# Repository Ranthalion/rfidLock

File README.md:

View this project on [CADLAB.io](https://cadlab.io/project/1244). 

# rfidLock
RFID Lock system

###Lock Hardware
The lock is [Morning Industry RF-01SN](https://www.amazon.com/gp/product/B000FBU2KW "Morning Industry RF-01SN").

###Lamp Server
Primary Network IP: 10.200.200.11 up on eth0   
Secure Network IP: 172.12.123.20 up on eth1   
Software: Apache2, php7 w/all mods and oauth extension, mariaDB, phpMyAdmin   
Services: SSHD   

### Diagram

### Database Diagram

### Installation

#### Configuration File

A configuration file is necessary for managing the connection to the mysql 
database which is used as the authoratative data source. This file is also 
needed for other configuration details such as the location of templates.

The options that can be configured in this file's database parameter match with mysql.connector's 
[Python Connection Arguments](https://dev.mysql.com/doc/connector-python/en/connector-python-connectargs.html)

A simple example configuration file is shown here for reference.

```json
{
  "database": {
    "username": "rfid_user",
    "password": "db_passwd",
    "host": "rfid_host",
    "database": "rfid_db"
  },
  "templates": "/usr/share/rfidlock/templates"
}
```

#### Member Server

To install the member server and web interface:

```bash
git clone https://github.com/Ranthalion/rfidLock.git
sudo pip install rfidLock/
# Edit or create the config.json file described above
vim /etc/rfidlock/config.json
# Creates the necessary database tables
rfid_db_install

# For Arch, this should enable wsgi
echo "LoadModule wsgi_module modules/mod_wsgi.so" >> /etc/httpd/conf/httpd.conf
# For Debian/Ubuntu, this should enable wsgi
a2enmod wsgi

# Mount the WSGI script, again, this is for Arch, will be different on other distros
echo "WSGIScriptAlias /rfid_db.wsgi $(which rfid_db.wsgi)" >> /etc/httpd/conf/httpd.conf

# Install and enable mod_wsgi
# Modify Apache server configuration

# TODO run a script that installs an apache server site to a path
# Varies by distribution

# ? WSGIScriptAlias /wsgi /path/to/script/rfid_members.wsgi
# TODO configure apache server to run mod_wsgi
```

To remove the member server after installation:

#### Raspberry Pi
Secure Network IP: 172.12.123.98
```bash
git clone https://github.com/Ranthalion/rfidLock.git
sudo pip install rfidLock/
# TODO, establish a daemon that handles the RFID lock and enable it on start-up
```

## Web API

### GET /api/verify  
Verifies access to a resource by rfid  
#### Consumes 
This API call consumes the following media types via the Content-Type request header:  
application/x-www-form-urlencoded  
#### Query parameters  
**resource (required)**  
Query Parameter — The name of the resource being requested  
**encryptedrfid (optional)**  
Query Parameter — The encoded rfid value  
**rfid (optional)**  
Query Parameter — The raw, unencoded rfid value  
#### Return type  
Content-Type: application/json  
```
{
  "verified" : false
}
```

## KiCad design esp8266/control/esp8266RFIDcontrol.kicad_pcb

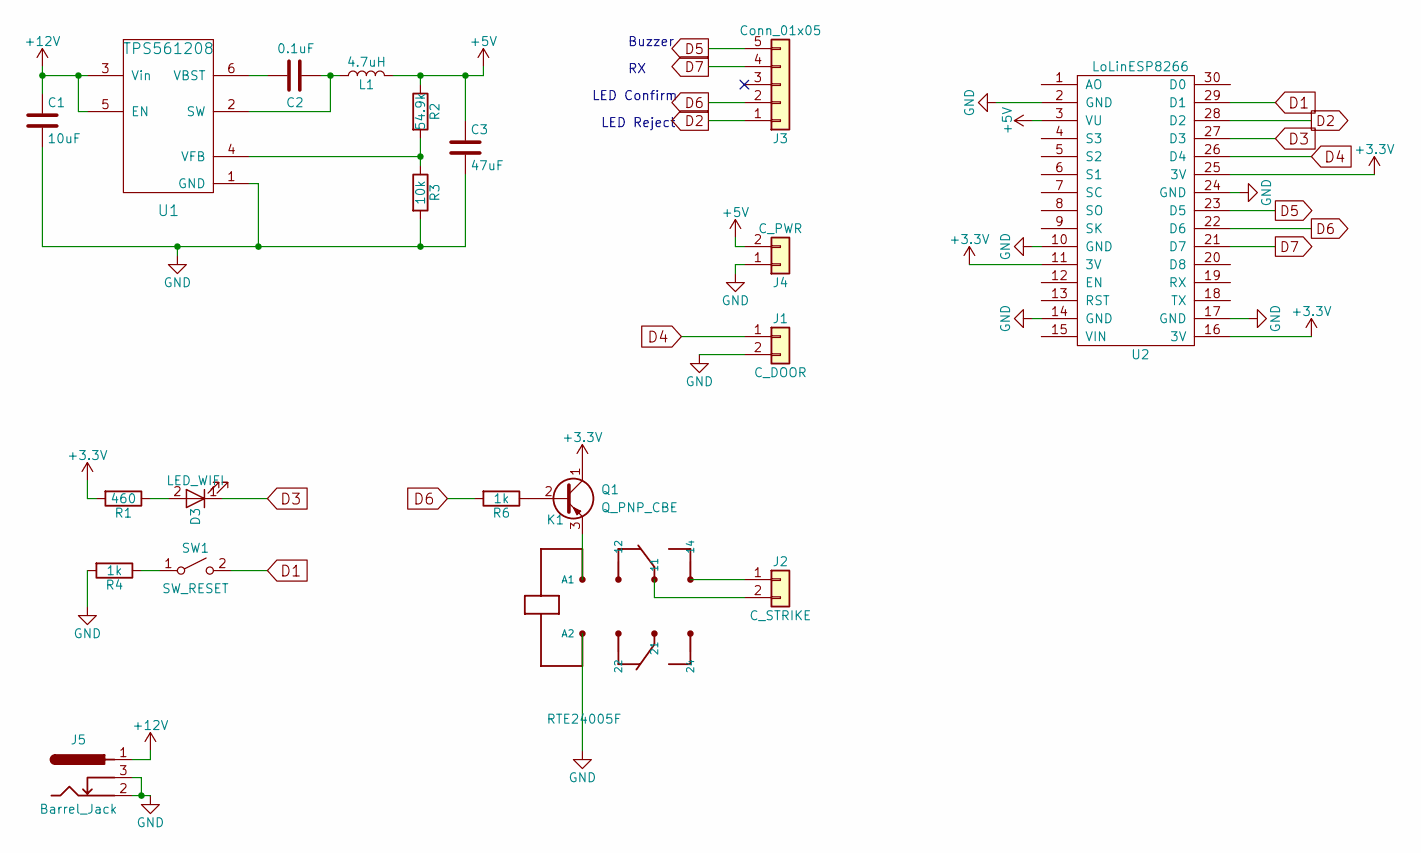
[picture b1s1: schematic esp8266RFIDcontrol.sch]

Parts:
C1: 10uF; C_1210_HandSoldering
C2: 0.1uF; C_1206_HandSoldering
C3: 47uF; C_1210_HandSoldering
D3: LED_WIFI; LED_0603_HandSoldering
J1: C_DOOR; CONNECTOR_JST_SH_2
J2: C_STRIKE; TerminalBlock_bornier-2_P5.08mm
J3: Conn_01x05; CONNECTOR_JST_SH_5
J4: C_PWR; CONNECTOR_JST_SH_2
J5: Barrel_Jack; BARREL_JACK
K1: RTE24005F
L1: 4.7uH; L_Wuerth_HCI-5040
Q1: Q_PNP_CBE; SOT-23_Handsoldering
R1: 460; R_0805_HandSoldering
R2: 54.9k; R_0805_HandSoldering; Tolerance 1%
R3: 10k; R_0805_HandSoldering; Tolerance 1%
R4, R6: 1k; R_0805_HandSoldering
SW1: SW_RESET; button_smd_2_pin
U1: TPS561208; SOT-23-6_Handsoldering
U2: LoLinESP8266; LOLIN_NODEMCU

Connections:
+3V3: Q1.1 (C), R1.2, U2.11 (3V), U2.16 (3V), U2.25 (3V)
+5V: C3.1, J4.2, L1.2, R2.1, U2.3 (VU)
+12V: C1.1, J5.1, U1.3 (Vin), U1.5 (EN)
D1: SW1.2 (B), U2.29 (D1)
D2: J3.1, U2.28 (D2)
D3: D3.1 (K), U2.27 (D3)
D4: J1.1, U2.26 (D4)
D5: J3.5, U2.23 (D5)
D6: J3.2, R6.2, U2.22 (D6)
D7: J3.4, U2.21 (D7)
GND: C1.2, C3.2, J1.2, J4.1, J5.2, J5.3, K1.A2, R3.2, R4.2, U1.1 (GND), U2.2 (GND), U2.10 (GND), U2.14 (GND), U2.17 (GND), U2.24 (GND)
unnamed: C2.1, L1.1, U1.2 (SW)
unnamed: C2.2, U1.6 (VBST)
unnamed: D3.2 (A), R1.1
unnamed: J2.1, K1.14
unnamed: J2.2, K1.11
unnamed: K1.A1, Q1.3 (E)
unnamed: Q1.2 (B), R6.1
unnamed: R2.2, R3.1, U1.4 (VFB)
unnamed: R4.1, SW1.1 (A)

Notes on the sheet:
Buzzer
LED Confirm
LED Reject

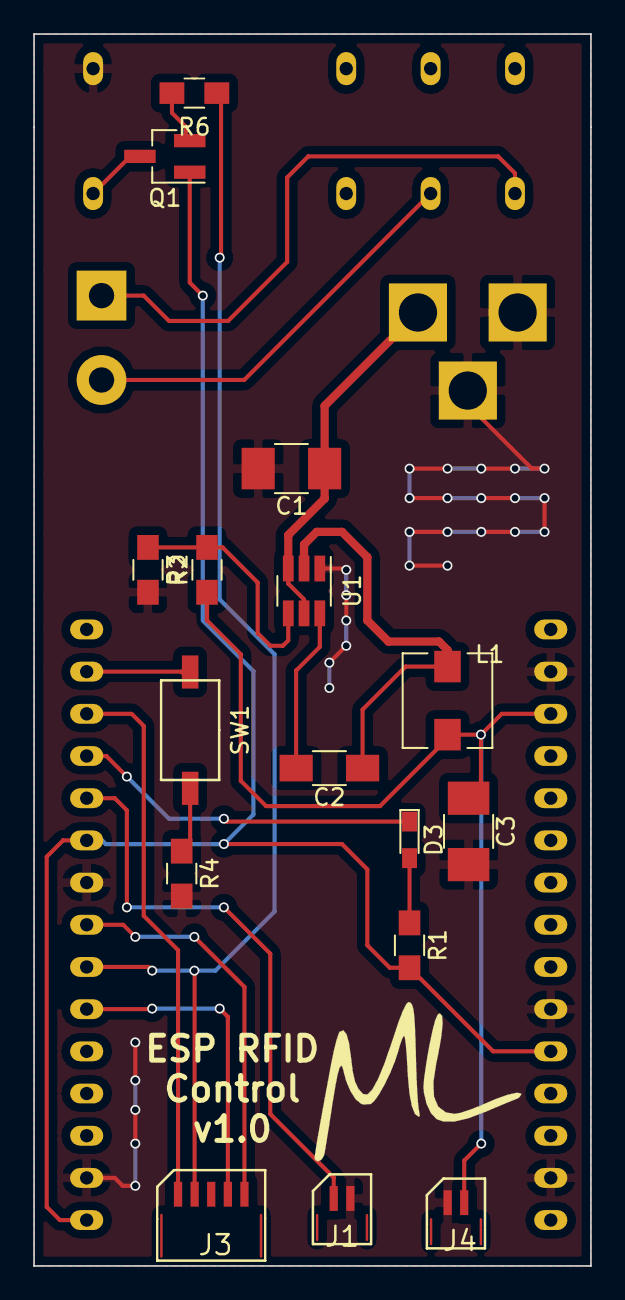
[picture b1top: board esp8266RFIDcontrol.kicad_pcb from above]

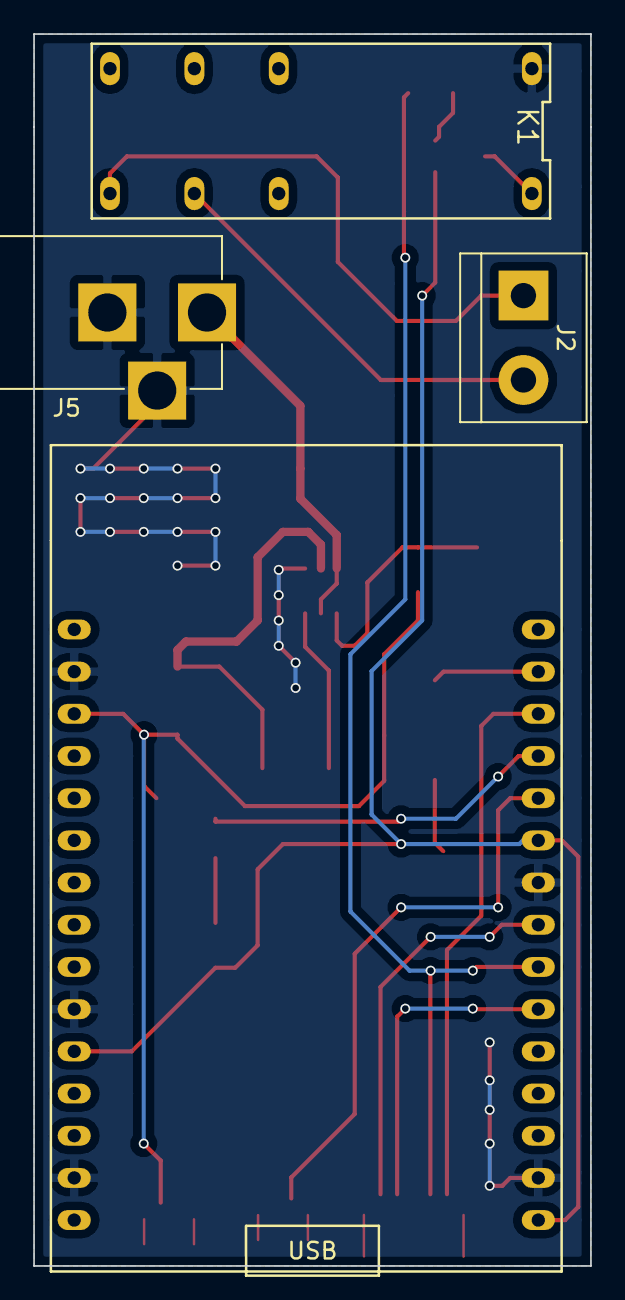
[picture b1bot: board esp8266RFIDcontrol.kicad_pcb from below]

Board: 2 copper layers, 33.5 x 74.2 mm, 20 parts (4 on the bottom side), 20 nets.

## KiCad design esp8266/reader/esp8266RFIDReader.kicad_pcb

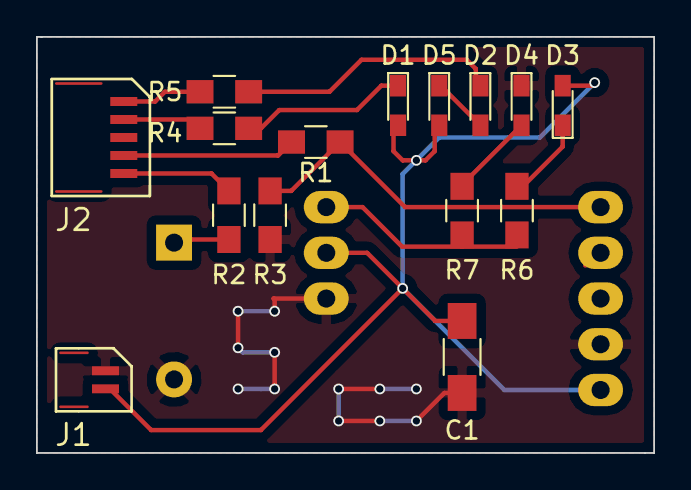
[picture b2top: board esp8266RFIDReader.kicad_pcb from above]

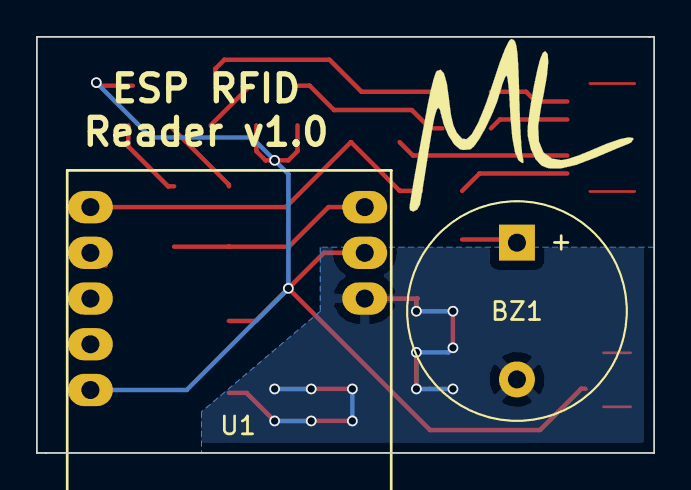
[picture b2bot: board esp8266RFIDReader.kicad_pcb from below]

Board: 2 copper layers, 34.3 x 23.1 mm, 17 parts (2 on the bottom side), 14 nets.

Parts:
BZ1: Buzzer; Buzzer_12x9.5RM7.6
C1: 0.1uF; C_1206_HandSoldering
D1: G; LED_0603_HandSoldering
D2, D5: R; LED_0603_HandSoldering
D3: B; LED_0603_HandSoldering
D4: Y; LED_0603_HandSoldering
J1: J1; CONNECTOR_JST_SH_2
J2: J2; CONNECTOR_JST_SH_5
R1: 10k; R_0805_HandSoldering
R2, R4, R5, R6, R7: 1k; R_0805_HandSoldering
R3: 20k; R_0805_HandSoldering
U1: RFID_MODULE_125_KHZ

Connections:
+5V: C1.1, D1.2, D3.2, D5.2, J1.2, U1.P1.5, U1.P3.2
Buzzer: J2.5, R2.2
GND: BZ1.2, C1.2, D4.1, J1.1, R3.1, U1.P1.4, U1.P3.3
LED_CONFIRM: J2.2, R4.2
LED_REJECT: J2.1, R5.2
unnamed: BZ1.1, R2.1
unnamed: D1.1, R4.1
unnamed: D2.1, R5.1
unnamed: D2.2, D5.1
unnamed: D3.1, R6.1
unnamed: D4.2, R7.1
unnamed: J2.4, R1.2
unnamed: R1.1, R3.2, U1.P1.1
unnamed: R6.2, R7.2, U1.P3.1

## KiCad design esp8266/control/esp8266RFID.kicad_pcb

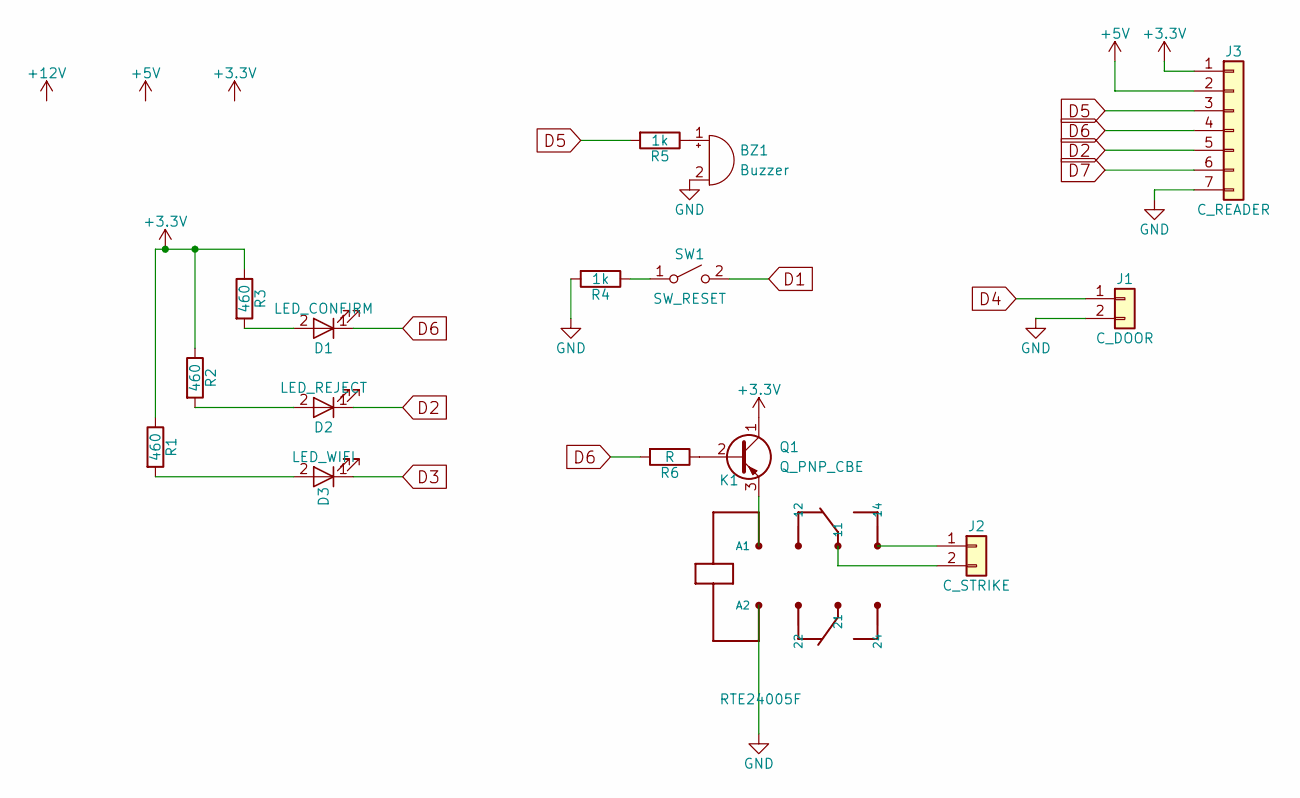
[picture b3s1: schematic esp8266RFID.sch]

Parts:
BZ1: Buzzer; BUZZER
D1: LED_CONFIRM; LED_1206_HandSoldering
D2: LED_REJECT; LED_1206_HandSoldering
D3: LED_WIFI; LED_1206_HandSoldering
J1: C_DOOR; Pin_Header_Angled_1x02_Pitch2.54mm
J2: C_STRIKE; Pin_Header_Angled_1x02_Pitch2.54mm
J3: C_READER; Pin_Header_Angled_1x07_Pitch2.54mm
K1: RTE24005F; RELAY_RTE24005F
Q1: Q_PNP_CBE; SOT-23_Handsoldering
R1, R2, R3: 460; R_1206_HandSoldering
R4, R5: 1k; R_1206_HandSoldering
R6: R; R_1206_HandSoldering
SW1: SW_RESET; button_smd_2_pin

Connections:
+3V3: J3.1, Q1.1 (C), R1.1, R2.1, R3.1
+5V: J3.2
D1: SW1.2 (B)
D2: D2.1 (K), J3.5
D3: D3.1 (K)
D4: J1.1
D5: J3.3, R5.2
D6: D1.1 (K), J3.4, R6.2
D7: J3.6
GND: BZ1.2 (+), J1.2, J3.7, K1.A2, R4.2
unnamed: BZ1.1 (-), R5.1
unnamed: D1.2 (A), R3.2
unnamed: D2.2 (A), R2.2
unnamed: D3.2 (A), R1.2
unnamed: J2.1, K1.14
unnamed: J2.2, K1.11
unnamed: K1.A1, Q1.3 (E)
unnamed: Q1.2 (B), R6.1
unnamed: R4.1, SW1.1 (A)

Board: 2 copper layers, 16 parts (0 on the bottom side), 14 nets, no tracks yet.

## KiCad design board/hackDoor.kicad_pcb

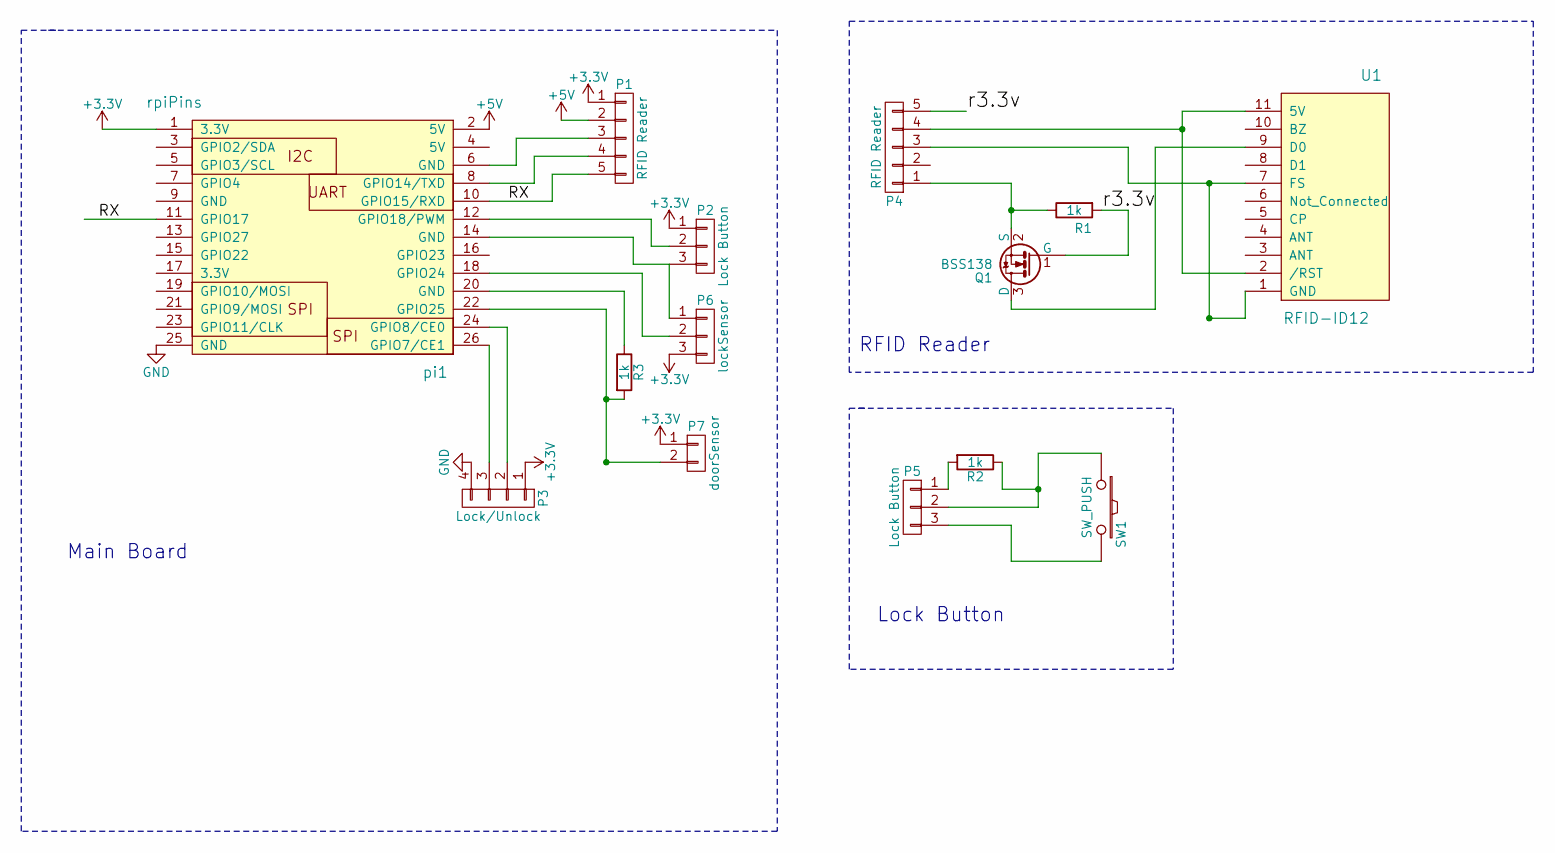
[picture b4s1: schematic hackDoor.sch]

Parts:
P1, P4: RFID Reader; Pin_Header_Angled_1x05
P2, P5: Lock Button; Pin_Header_Angled_1x03
P3: Lock/Unlock; Pin_Header_Angled_1x04
P6: lockSensor; Pin_Header_Angled_1x03
P7: doorSensor; Pin_Header_Angled_1x02
Q1: BSS138; SOT-23
R1, R2, R3: 1k; R_0805_HandSoldering
SW1: SW_PUSH
U1: RFID-ID12; rfid-id12
pi1: rpiPins; Pin_Header_Straight_2x13

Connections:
+3V3: P1.1, P2.1, P3.1, P6.3, P7.1, pi1.1 (3.3V)
+5V: P1.2, pi1.2 (5V)
/RX: P1.5, pi1.10 (GPIO15/RXD), pi1.11 (GPIO17)
/r3.3v: P4.5, Q1.1 (G), R1.2
GND: P3.4, pi1.25 (GND)
unnamed: P1.3, pi1.6 (GND)
unnamed: P1.4, pi1.8 (GPIO14/TXD)
unnamed: P2.2, pi1.12 (GPIO18/PWM)
unnamed: P2.3, P6.1, pi1.14 (GND)
unnamed: P3.2, pi1.24 (GPIO8/CE0)
unnamed: P3.3, pi1.26 (GPIO7/CE1)
unnamed: P4.1, Q1.2 (S), R1.1
unnamed: P4.3, U1.1 (GND), U1.7 (FS)
unnamed: P4.4, U1.2 (/RST), U1.11 (5V)
unnamed: P5.1, R2.2
unnamed: P5.2, R2.1, SW1.1
unnamed: P5.3, SW1.2
unnamed: P6.2, pi1.18 (GPIO24)
unnamed: P7.2, R3.2, pi1.22 (GPIO25)
unnamed: Q1.3 (D), U1.9 (D0)
unnamed: R3.1, pi1.20 (GND)

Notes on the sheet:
Main Board
RFID Reader
Lock Button

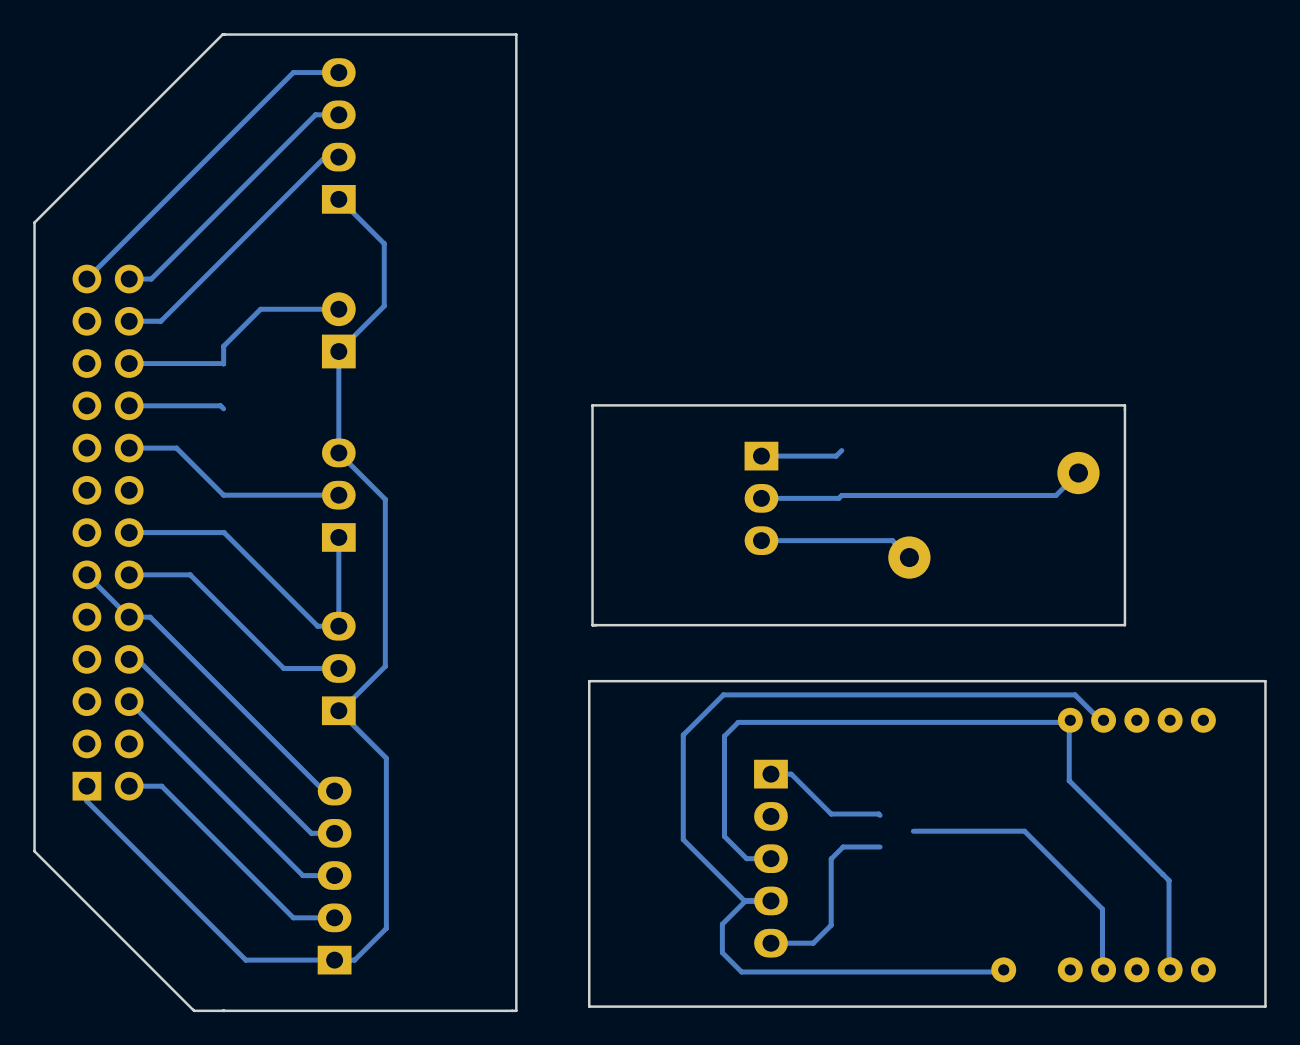
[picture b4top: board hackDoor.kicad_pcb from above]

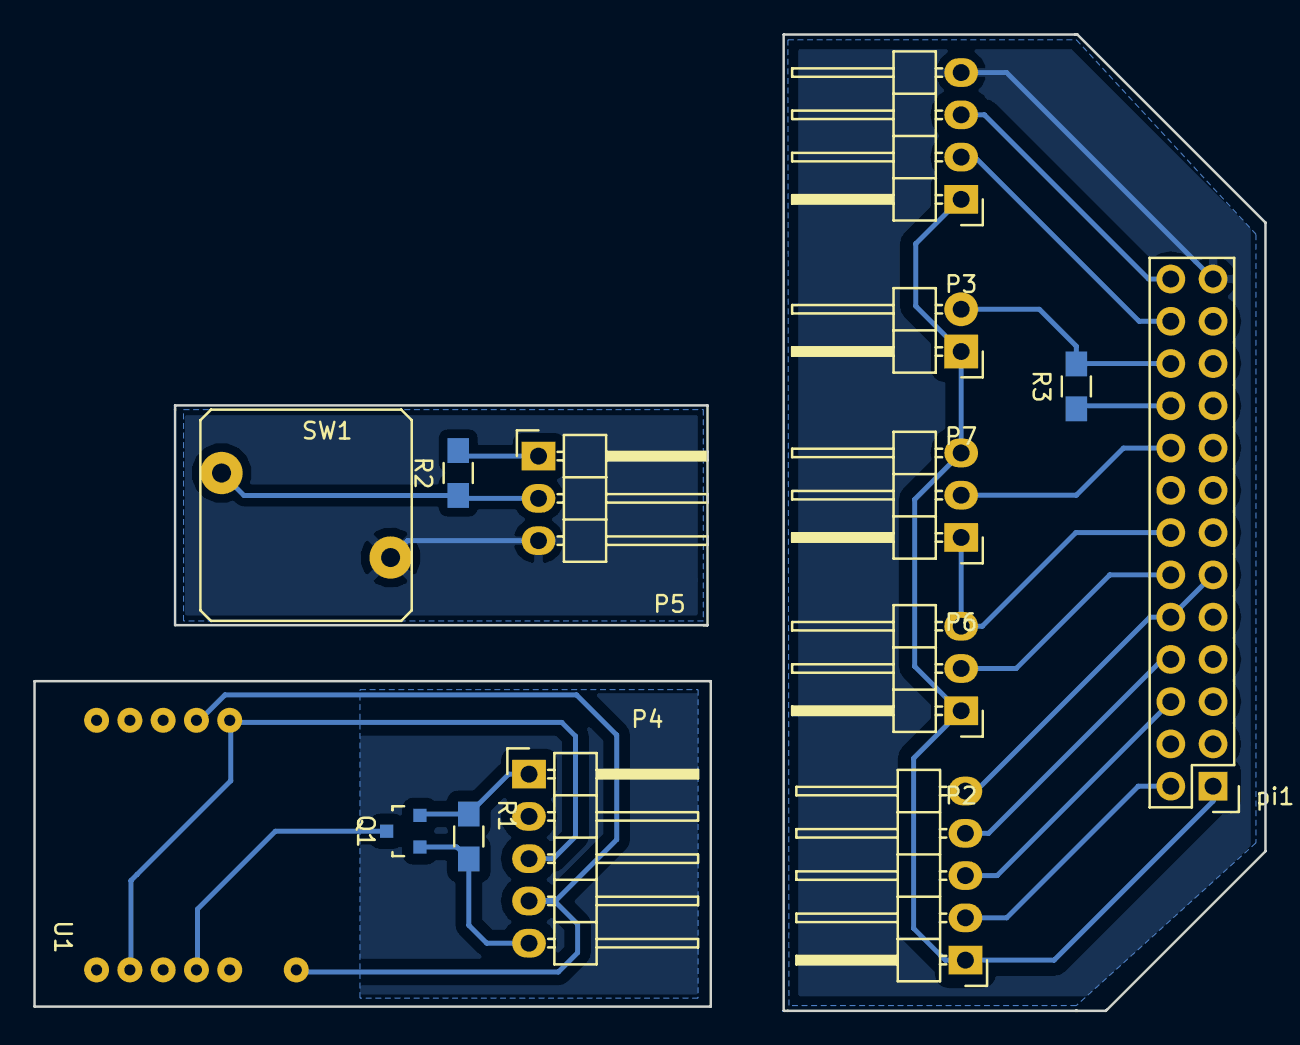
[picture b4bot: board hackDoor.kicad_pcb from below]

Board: 2 copper layers, 74.0 x 58.7 mm, 14 parts (14 on the bottom side), 21 nets.

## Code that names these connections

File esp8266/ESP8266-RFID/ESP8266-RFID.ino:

#include <FS.h>

#include <stdlib.h>
#include <Ticker.h>
#include <SoftwareSerial.h>
#include <ESP8266WiFi.h>
#include <DNSServer.h>
#include <ESP8266WebServer.h>
#include <WiFiManager.h>
#include <ArduinoJson.h>
#include <ESP8266HTTPClient.h>
#include <SPI.h>

const byte RESET_BUTTON = D1;
const byte LED_WIFI     = D3;
const byte DOOR_SENSOR  = D4; //Seems to cause a problem at power up
const byte BUZZER       = D5;
const byte SW_RX        = D7;
const byte SW_TX        = D8;
const byte LED_REJECT   = D2;
const byte LED_CONFIRM  = D6;

//Range 100 to 5000 Hz
unsigned int GOOD_TONE = 1500;
unsigned int BAD_TONE = 100;
unsigned int DEFAULT_TONE = 1000;

unsigned long SHORT_DURATION = 200;
unsigned long MEDIUM_DURATION = 500;
unsigned long LONG_DURATION = 700;

char verify_url[80];
char resource_name[80];

Ticker ticker;
int count = 0;
int confirmCount = 0;
int rejectCount = 0;

long rfid;
String inputString = "";         // a String to hold incoming data
boolean stringComplete = false;  // whether the string is complete
boolean connectedToWifi = false;
bool shouldSaveConfig = false;

SoftwareSerial swSerial(SW_RX, SW_TX);

bool loadConfig() {

  File configFile = SPIFFS.open("/config.json", "r");
  if (!configFile) {
    Serial.println("Failed to open config file");
    return false;
  }

  size_t size = configFile.size();
  if (size > 1024) {
    Serial.println("Config file size is too large");
    return false;
  }

  std::unique_ptr<char[]> buf(new char[size]);
  configFile.readBytes(buf.get(), size);

  DynamicJsonDocument jsonBuffer;
  DeserializationError error = deserializeJson(jsonBuffer, buf.get());
  if (error) {
    Serial.println("Unable to deserialize");
    return false;
  }

  JsonObject& json = jsonBuffer.as<JsonObject>();
  if (json.success()) {
    strcpy(verify_url, json["verify_url"]);
    strcpy(resource_name, json["resource_name"]);
    return true;
  } else {
    Serial.println("failed to parse json config");
    return false;
  }
}

bool writeConfig(){
  DynamicJsonDocument jsonBuffer;
  JsonObject& json = jsonBuffer.to<JsonObject>();
  json["verify_url"] = verify_url;
  json["resource_name"] = resource_name;

  File configFile = SPIFFS.open("/config.json", "w");
  if (!configFile) {
    Serial.println("failed to open config file for writing");
    return false;
  }

  serializeJson(json, configFile);
  serializeJson(jsonBuffer, Serial);
  configFile.close();
  
  return true;
}

void setup() {

  // Set up GPIO
  digitalWrite(LED_WIFI, HIGH);
  digitalWrite(LED_CONFIRM, HIGH);  
  digitalWrite(LED_REJECT, HIGH);
  pinMode(LED_WIFI, OUTPUT);
  pinMode(LED_CONFIRM, OUTPUT);
  pinMode(LED_REJECT, OUTPUT);
  pinMode(RESET_BUTTON, INPUT_PULLUP);
  pinMode(DOOR_SENSOR, INPUT_PULLUP);
  pinMode(BUZZER, OUTPUT);

  start_up_tone();
  
  // Set up timer
  ticker.attach(0.25, timer_tick);  
  
  // Set up serial
  inputString.reserve(200);
  Serial.begin(9600);
  swSerial.begin(9600);

  //Read configuration data
  if (!SPIFFS.begin()) {
    error_tone();
    Serial.println("Failed to mount file system");
    return;
  }
  
  if (!loadConfig()) {
    Serial.println("Failed to load config");
  } else {
    Serial.println("Config loaded");
  }
  
  
  // Set up wifi 
  connectedToWifi = false;
  WiFiManager wifiManager;
  wifiManager.setDebugOutput(false);
  
  wifiManager.setSaveConfigCallback(saveConfigCallback);
  WiFiManagerParameter verify_url_param("url", "verify url", verify_url, 80);
  wifiManager.addParameter(&verify_url_param);
  WiFiManagerParameter resource_name_param("name", "resource name", resource_name, 80);
  wifiManager.addParameter(&resource_name_param);
  
  //reset wifi settings if button is pressed
  if (digitalRead(RESET_BUTTON) == LOW)
  {
    tone(BUZZER, BAD_TONE, LONG_DURATION);
    wifiManager.resetSettings();
    SPIFFS.format();
  }

  wifiManager.autoConnect("RFID Setup");
  connectedToWifi = true;
  tone(BUZZER, GOOD_TONE, SHORT_DURATION);
  
  strcpy(verify_url, verify_url_param.getValue());
  strcpy(resource_name, resource_name_param.getValue());

  //save the custom parameters to FS
  if (shouldSaveConfig) {
    Serial.println("Saving Config");
    
    if (!writeConfig()) {
      Serial.println("Failed to load config");
    } else {
      Serial.println("Config saved");
    }
  }
}

void loop() {

  char x[15];

   while (swSerial.available()) {
    char inChar = (char)swSerial.read();
    inputString += inChar;

    //Hacky way to read all the bytes from a single fob
    if (inputString.length() >= 14){
      //Hack to ignore start byte, version/customer Id, checksum, and stop byte
      inputString = inputString.substring(5, 11);

      //Convert the ascii hex value into a decimal number
      inputString.toCharArray(x, 7);
      rfid = strtol(x, NULL, 16);
      
      stringComplete = true;
    }
  }
  
  if (stringComplete) {
    
    //Call web api to verify rfid
    
    //TODO: Do something with an indicator LED to show pending
    tone(BUZZER, DEFAULT_TONE, 75);
    HTTPClient http;

    //Convert the decimal to string
    ltoa(rfid, x, 10);

    String payload = "?rfid=" + urlencode(x) + "&resource=" + urlencode(resource_name);
    String url = verify_url;

    http.begin(url + payload);
    int httpCode = http.GET();

    // httpCode will be negative on error
    if(httpCode == HTTP_CODE_OK) {
      String payload = http.getString();
      
      DynamicJsonDocument jsonBuffer;
      DeserializationError error = deserializeJson(jsonBuffer, payload.c_str());
      if (error) {
        //TODO: Handle error
        error_tone();
      }

      JsonObject& json = jsonBuffer.as<JsonObject>();
      
      if (json.success()) {
        bool verified = json["verified"];
        if (verified == true)
        {
          confirmCount = 16;
          tone(BUZZER, GOOD_TONE, MEDIUM_DURATION);
          //Unlock
        }
        else
        {
          rejectCount = 6;
          tone(BUZZER, BAD_TONE, LONG_DURATION);
        }
        
      } else {
        //TODO: Locally keep track of the error for whatever reason
        Serial.println("failed to parse response");
        error_tone();
      }
      //TODO: Parse as JSON and see if verified is true
      
    } else {
      Serial.printf("[HTTP] GET... failed, error: %s\n", http.errorToString(httpCode).c_str());
      //TODO: Locally keep track of the error for whatever reason
      error_tone();
    }

    http.end();

    inputString = "";
    stringComplete = false;
  }
}

void timer_tick()
{
  ++count;
  
  if (connectedToWifi == true)
  {
    //connected to wifi
    digitalWrite(LED_WIFI, HIGH);
  }
  else
  {
    //searching for wifi
    digitalWrite(LED_WIFI, ((count & 0x01) == 0));
  }

  if (confirmCount > 0)
  {
    digitalWrite(LED_CONFIRM, LOW);
    confirmCount--;
  }
  else
  {
    digitalWrite(LED_CONFIRM, HIGH);
  }

  if (rejectCount > 0)
  {
    digitalWrite(LED_REJECT, LOW);
    rejectCount--;
  }
  else if(rejectCount == 0)
  {
    digitalWrite(LED_REJECT, HIGH);
  }

  //TODO: Monitor the door sensor and report prolonged open states
}

void saveConfigCallback () {
  shouldSaveConfig = true;
}

String urlencode(String str)
{
    String encodedString="";
    char c;
    char code0;
    char code1;

    for (int i =0; i < str.length(); i++){
      c=str.charAt(i);
      if (c == ' '){
        encodedString+= '+';
      } else if (isalnum(c)){
        encodedString+=c;
      } else{
        code1=(c & 0xf)+'0';
        if ((c & 0xf) >9){
            code1=(c & 0xf) - 10 + 'A';
        }
        c=(c>>4)&0xf;
        code0=c+'0';
        if (c > 9){
            code0=c - 10 + 'A';
        }
        encodedString+='%';
        encodedString+=code0;
        encodedString+=code1;
      }
      yield();
    }
    return encodedString;    
}

void start_up_tone(){
  tone(BUZZER, BAD_TONE);
  delay(100);

  tone(BUZZER, DEFAULT_TONE);
  delay(100);
  
  tone(BUZZER, GOOD_TONE);
  delay(150);
  noTone(BUZZER);  
}

void error_tone()
{
  tone(BUZZER, BAD_TONE);
  delay(SHORT_DURATION);
  noTone(BUZZER);
  delay(SHORT_DURATION);
  tone(BUZZER, BAD_TONE, SHORT_DURATION);
}

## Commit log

2016-09-25 added python code to: read rfids from the serial port check rfid against sqlite users database read button press for locking the door lock and unlock door
2016-09-30 adding kicad files
2016-10-02 added secondary schematics. added netlist and footprint association. started pcb layout.
2016-10-02 Add diagram to readme
2016-10-07 Added code for reading and writing to member database
2016-10-07 Reorganized into a proper python package, starting tests
2016-10-08 Members adding and checking are tested and work
2016-10-08 Database cloning tests are completed
2016-10-12 DoorConnection object is tested and shown to work
2016-10-14 Added basic install scripts
2016-10-14 Added sufficient information for pip installation
2016-10-14 Pip install works better, starting toward integration with Apache
2016-10-15 Using Jinja for page generation
2016-10-17 app setup, db structure, and data seeds
2016-10-17 Auth and Add Member stub
2016-10-17 Database management page should now work
2016-10-21 Edit resources
2016-10-22 Restore member
2016-10-24 PayPal lookup and public member activation
2016-10-24 updated env.example to include paypal keys
2016-10-24 Automated welcome email
2016-10-24 Fixed database removal script
2016-10-24 Reform Max's rpiCode into Door class integrated with database system and a run script
2016-10-25 Created install instructions with better details
2016-10-26 Rewrote to support Python 2
2016-10-26 Fixed small mistake in test code breaking in Python 3
2016-10-26 Created install script
2016-10-26 Moved template files to be explicitly part of rfidLock module
2016-10-27 Stripped out superfluous portions of Python code and switched from revokation to expiration
2016-10-27 Fixed glitch in setup.py
2016-10-27 Moving rfid entry to last step of public member registration
2016-10-27 Various minor script changes
2016-10-28 finished preliminary board routing. added rfid reader footprint
2016-10-28 some routing changes for the board
2016-10-28 hashing rfid and other small tweaks
2016-10-29 changed trace width to .30 mm
2016-10-29 Added support for separate resources
2016-10-29 Accomodate changing membership table in database install script
2016-10-29 Fixed name mistake in db install script
2016-10-29 adding fabrication outputs
2016-10-29 Fixed rfid_db_install to use resource
2016-10-29 Added sync command line command
2016-10-31 Quickbooks integration
2016-10-31 Add QBO to public add
2016-11-03 Slack Invite
2016-11-03 Update member key
2016-11-05 removed copper pour from under rfid module. detached copper pour on rfid reader board from ground net
2016-11-05 routing change
2016-11-06 Validation moved to Requests and added middleware for date and rfid
2016-11-06 Using requess for validation
2016-11-06 Error page
2016-11-06 add mailchimp and move emails and subscriptions to use queued events
2016-11-07 Scripts and resource updates
2016-11-11 Initial Membership Summary Report
2016-11-11 added door and lock sensors. fixed the logic converter circuit on the rfid board
2016-11-20 Payment Importer and scheduled job
2016-11-20 member tied to customer. Add payment report.
2016-11-21 Update case for listeners
2016-11-27 Failed Quickbooks emails and job
2016-11-30 Pending Revokation
2016-12-24 added mirrored fab outputs and increased pad diameter on rfid module
2016-12-31 Update README.md
    adding rpi ip address
2017-01-01 using the parameters for start_tx_pin and lock_button_pin in the Door class init. changing the raspberryPi template to reflect the pin mapping on the board
2017-01-15 fixing schema of local database and querys to match the server view
2017-01-17 Add logging, resize portion of tag read, and correct expiration_date to expire_date
2017-01-17 logging, not logger
2017-01-17 Update rfid value encoding to match rpi and fix bug where member name may not be different
2017-01-19 Switched RFID string for better consistency
2017-01-21 Sync rfid encoding between web app and rpi
2017-01-21 Fixing stupid mistake
2017-09-24 Add verify api method
2017-10-16 Add logging to verfication requests
2017-10-16 Event logging
2017-10-17 Initial ESP8266 device firmware for lock
2017-11-12 Adding web api to readme
2017-11-12 fix readme markdown
2018-04-07 Support for new reader + paypal update
    Adding support for new RFID reader and modifying paypal queries. Also updated vagrantfile to perform additional provisioning.
2018-04-19 Renewal letter & updates to payment importer command
    Added templates for renewal email, as well as command for sending renewal email. Integrated with mailgun.
2018-04-19 Fix HB event log causing truncation error
    Fix HB event log causing truncation error
2018-06-10 ESP8266 RFID reader sketch
    Updated sketch for ESP8266 based rfid reader. Added buzzer, indicator lights, and relay control.
2018-06-16 Schematic and PCB for RFID reader module + WIP for ESP board/module
2018-06-21 Schematic and PCB for RFID control module.
2018-08-04 Backlink to CADLAB.io has been added.
2018-11-22 ESP8266 RFID reader board
2018-11-22 Add app.grant_duration config to control Avea grant time
2020-09-09 adding a docker-compose setup to make it easier for developers to stand up the app
2020-09-09 Bump marked from 0.3.6 to 0.3.19 in /webCode/membership
    Bumps [marked](https://github.com/markedjs/marked) from 0.3.6 to 0.3.19.
    - [Release notes](https://github.com/markedjs/marked/releases)
    - [Commits](https://github.com/markedjs/marked/compare/v0.3.6...v0.3.19)
2020-09-09 Bump stringstream from 0.0.5 to 0.0.6 in /webCode/membership
    Bumps [stringstream](https://github.com/mhart/StringStream) from 0.0.5 to 0.0.6.
    - [Release notes](https://github.com/mhart/StringStream/releases)
    - [Commits](https://github.com/mhart/StringStream/compare/v0.0.5...v0.0.6)
2020-09-09 Bump lodash from 4.16.4 to 4.17.19 in /webCode/membership
    Bumps [lodash](https://github.com/lodash/lodash) from 4.16.4 to 4.17.19.
    - [Release notes](https://github.com/lodash/lodash/releases)
    - [Commits](https://github.com/lodash/lodash/compare/4.16.4...4.17.19)
2020-09-09 Bump is-my-json-valid from 2.15.0 to 2.20.5 in /webCode/membership
    Bumps [is-my-json-valid](https://github.com/mafintosh/is-my-json-valid) from 2.15.0 to 2.20.5.
    - [Release notes](https://github.com/mafintosh/is-my-json-valid/releases)
    - [Commits](https://github.com/mafintosh/is-my-json-valid/compare/v2.15.0...v2.20.5)
2020-09-15 setting up some events and listeners to fire email notifications
2020-09-16 push to resource - an access list will now push to a resource when a network address is configured for that resource. - added doorDummy to help with testing - setting up events and listeners for heal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
2020-09-17 Bump flask from 0.10.1 to 1.0 in /doorDummy
    Bumps [flask](https://github.com/pallets/flask) from 0.10.1 to 1.0.
    - [Release notes](https://github.com/pallets/flask/releases)
    - [Changelog](https://github.com/pallets/flask/blob/master/CHANGES.rst)
    - [Commits](https://github.com/pallets/flask/compare/0.10.1...1.0)
2020-12-11 Bump ini from 1.3.4 to 1.3.7 in /webCode/membership
    Bumps [ini](https://github.com/isaacs/ini) from 1.3.4 to 1.3.7.
    - [Release notes](https://github.com/isaacs/ini/releases)
    - [Commits](https://github.com/isaacs/ini/compare/v1.3.4...v1.3.7)
2021-03-09 Bump elliptic from 6.3.2 to 6.5.4 in /webCode/membership
    Bumps [elliptic](https://github.com/indutny/elliptic) from 6.3.2 to 6.5.4.
    - [Release notes](https://github.com/indutny/elliptic/releases)
    - [Commits](https://github.com/indutny/elliptic/compare/v6.3.2...v6.5.4)
2021-03-30 Bump y18n from 3.2.1 to 3.2.2 in /webCode/membership
    Bumps [y18n](https://github.com/yargs/y18n) from 3.2.1 to 3.2.2.
    - [Release notes](https://github.com/yargs/y18n/releases)
    - [Changelog](https://github.com/yargs/y18n/blob/master/CHANGELOG.md)
    - [Commits](https://github.com/yargs/y18n/commits)
2021-05-06 Bump underscore from 1.8.3 to 1.13.1 in /webCode/membership
    Bumps [underscore](https://github.com/jashkenas/underscore) from 1.8.3 to 1.13.1.
    - [Release notes](https://github.com/jashkenas/underscore/releases)
    - [Commits](https://github.com/jashkenas/underscore/compare/1.8.3...1.13.1)
2021-05-09 Bump lodash from 4.17.19 to 4.17.21 in /webCode/membership
    Bumps [lodash](https://github.com/lodash/lodash) from 4.17.19 to 4.17.21.
    - [Release notes](https://github.com/lodash/lodash/releases)
    - [Commits](https://github.com/lodash/lodash/compare/4.17.19...4.17.21)
2021-05-10 Bump hosted-git-info from 2.1.5 to 2.8.9 in /webCode/membership
    Bumps [hosted-git-info](https://github.com/npm/hosted-git-info) from 2.1.5 to 2.8.9.
    - [Release notes](https://github.com/npm/hosted-git-info/releases)
    - [Changelog](https://github.com/npm/hosted-git-info/blob/v2.8.9/CHANGELOG.md)
    - [Commits](https://github.com/npm/hosted-git-info/compare/v2.1.5...v2.8.9)
2021-08-04 Bump tar from 2.2.1 to 2.2.2 in /webCode/membership
    Bumps [tar](https://github.com/npm/node-tar) from 2.2.1 to 2.2.2.
    - [Release notes](https://github.com/npm/node-tar/releases)
    - [Changelog](https://github.com/npm/node-tar/blob/main/CHANGELOG.md)
    - [Commits](https://github.com/npm/node-tar/compare/v2.2.1...v2.2.2)
    ---
    updated-dependencies:
2022-03-29 Bump guzzlehttp/psr7 from 1.4.2 to 1.8.5 in /webCode/membership
    Bumps [guzzlehttp/psr7](https://github.com/guzzle/psr7) from 1.4.2 to 1.8.5.
    - [Release notes](https://github.com/guzzle/psr7/releases)
    - [Changelog](https://github.com/guzzle/psr7/blob/1.8.5/CHANGELOG.md)
    - [Commits](https://github.com/guzzle/psr7/compare/1.4.2...1.8.5)
    ---
    updated-dependencies:
2022-05-25 Bump guzzlehttp/guzzle from 6.3.2 to 6.5.6 in /webCode/membership
    Bumps [guzzlehttp/guzzle](https://github.com/guzzle/guzzle) from 6.3.2 to 6.5.6.
    - [Release notes](https://github.com/guzzle/guzzle/releases)
    - [Changelog](https://github.com/guzzle/guzzle/blob/6.5.6/CHANGELOG.md)
    - [Commits](https://github.com/guzzle/guzzle/compare/6.3.2...6.5.6)
    ---
    updated-dependencies:
2022-06-10 Bump guzzlehttp/guzzle from 6.3.2 to 6.5.7 in /webCode/membership
    Bumps [guzzlehttp/guzzle](https://github.com/guzzle/guzzle) from 6.3.2 to 6.5.7.
    - [Release notes](https://github.com/guzzle/guzzle/releases)
    - [Changelog](https://github.com/guzzle/guzzle/blob/6.5.7/CHANGELOG.md)
    - [Commits](https://github.com/guzzle/guzzle/compare/6.3.2...6.5.7)
    ---
    updated-dependencies:
2022-06-21 Bump guzzlehttp/guzzle from 6.3.2 to 6.5.8 in /webCode/membership
    Bumps [guzzlehttp/guzzle](https://github.com/guzzle/guzzle) from 6.3.2 to 6.5.8.
    - [Release notes](https://github.com/guzzle/guzzle/releases)
    - [Changelog](https://github.com/guzzle/guzzle/blob/6.5.8/CHANGELOG.md)
    - [Commits](https://github.com/guzzle/guzzle/compare/6.3.2...6.5.8)
    ---
    updated-dependencies:
2022-06-28 Bump deap from 1.0.0 to 1.0.1 in /webCode/membership
    Bumps [deap](https://github.com/selfcontained/deap) from 1.0.0 to 1.0.1.
    - [Release notes](https://github.com/selfcontained/deap/releases)
    - [Commits](https://github.com/selfcontained/deap/commits)
    ---
    updated-dependencies:
    - dependency-name: deap
2022-12-06 Bump qs from 6.2.1 to 6.2.4 in /webCode/membership
    Bumps [qs](https://github.com/ljharb/qs) from 6.2.1 to 6.2.4.
    - [Release notes](https://github.com/ljharb/qs/releases)
    - [Changelog](https://github.com/ljharb/qs/blob/main/CHANGELOG.md)
    - [Commits](https://github.com/ljharb/qs/compare/v6.2.1...v6.2.4)
    ---
    updated-dependencies:
